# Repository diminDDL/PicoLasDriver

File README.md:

# Picolas Laser Diode Controller/Driver

This repository houses the necessary components for a touchscreen-based controller/driver for the Picolas series of laser diode boards, including hardware schematics, embedded firmware, and a Python GUI.

## Features

- Supports control of analog models with trigger pins and analog voltage for adjusting the current setpoint.
- Designed to work seamlessly with a Raspberry Pi SBC and a touchscreen.
- Configuration flexibility through JSON file.

## Getting Started

### Prerequisites

- Raspberry Pi with a touchscreen
- Picolas series laser diode board (analog models with trigger pins)

### Installation

1. Clone the repository.
2. Follow the setups in [howto.md](https://github.com/diminDDL/PicoLasDriver/blob/main/howto.md)
3. Configure a startup script to initiate the Python program automatically on boot. Additionally, it's advisable to disable the touchscreen until the program starts.
4. Consider enabling the overlay filesystem to safeguard your data.

## GUI Layout & Functions

- **"+" and "-" buttons**: Increase or decrease values. They accelerate when held.
- **"Single/Pulsed" modes**: Toggle single pulse operation.
- **"Global/Local pulse count"**: View total pulse count and current session count.
- **"ADC readout"**: Display the raw 12-bit ADC value from the photodiode amplifier.
- **"Lock icon"**: Lock or unlock the device to prevent accidental value changes.
- **"IO1-4"**: IO pin toggle buttons.
- **"Enable/Disable"**: Control the pulse output.
- **Error readout**: Reads out the errors and other state information.

⚠️ **Important**: It is recommended to turn off the output when adjusting settings to prevent potential glitches on the output.

## Hardware & Communication

- The board connects to the Raspberry Pi via USB, with a communication frequency of every 100ms.
- Auto-reconnect and fault indications in the Python GUI.
- LED indicators for the board's internal states.
- GPIO pins provide a high impedance 5V when active.
- Over-voltage protection up to 5V.
- Photodiode amplifier module design and guidance provided.

### Pinout of the connector:

## Operating Mechanism

The board keeps the Picolas driver's enable pin high and uses the trigger pin to generate impulses. An analog DAC sets the voltage to control the output current limit. If the E-STOP pin is triggered, the system becomes non-functional until a power cycle.

## License

This project is licensed under the MIT License.

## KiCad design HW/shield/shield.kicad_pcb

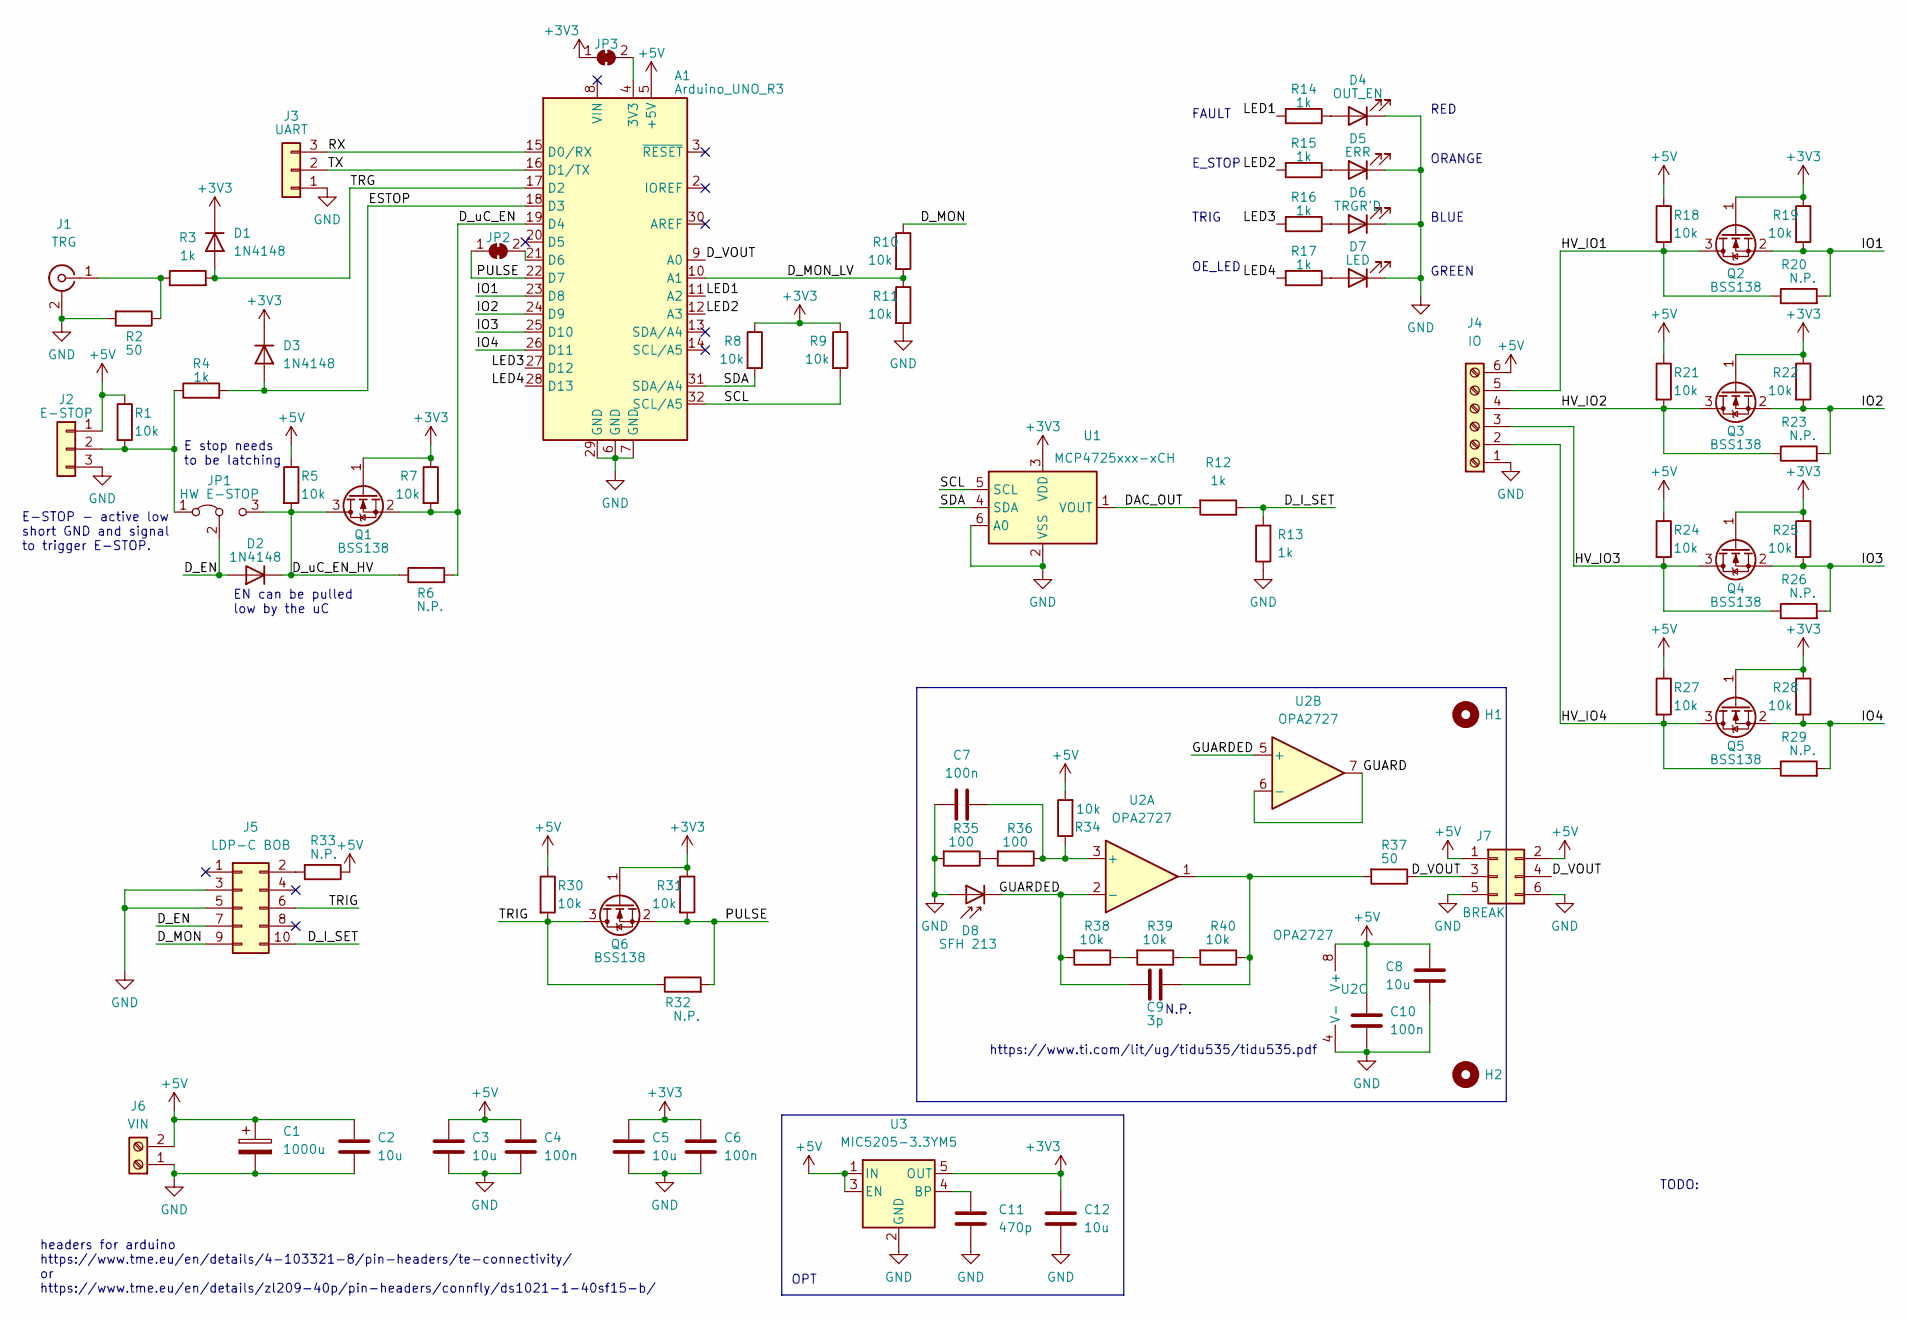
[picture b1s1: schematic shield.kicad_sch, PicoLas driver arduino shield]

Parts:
A1: Arduino_UNO_R3
C1: 1000u; CP_Elec_10x10
C2, C3, C5, C8, C12: 10u; C_0805_2012Metric_Pad1.18x1.45mm_HandSolder
C4, C6, C7, C10: 100n; C_0805_2012Metric_Pad1.18x1.45mm_HandSolder
C9: 3p; C_0805_2012Metric_Pad1.18x1.45mm_HandSolder
C11: 470p; C_0805_2012Metric_Pad1.18x1.45mm_HandSolder
D1, D2, D3: 1N4148; D_SOD-123
D4: OUT_EN; LED_0805_2012Metric_Pad1.15x1.40mm_HandSolder
D5: ERR; LED_0805_2012Metric_Pad1.15x1.40mm_HandSolder
D6: TRGR'D; LED_0805_2012Metric_Pad1.15x1.40mm_HandSolder
D7: LED; LED_0805_2012Metric_Pad1.15x1.40mm_HandSolder
D8: SFH 213; LED_D5.0mm_IRGrey
H1, H2: MountingHole; MountingHole_3.2mm_M3
J1: TRG; SMA_Amphenol_901-144_Vertical
J2: E-STOP; TerminalBlock_Altech_AK300-3_P5.00mm
J3: UART; PinSocket_1x03_P2.54mm_Vertical
J4: IO; Altech_AK300_1x06_P5.00mm_45-Degree
J5: LDP-C BOB; PinHeader_2x05_P2.54mm_Vertical
J6: VIN; TerminalBlock_Altech_AK300-2_P5.00mm
J7: BREAK; PinSocket_2x03_P2.54mm_Vertical
JP1: HW E-STOP; SolderJumper-3_P1.3mm_Bridged12_RoundedPad1.0x1.5mm_NumberL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
JP2, JP3: INTR; SolderJumper-2_P1.3mm_Bridged2Bar_RoundedPad1.0x1.5mm
Q1, Q2, Q3, Q4, Q5, Q6: BSS138; SOT-23
R1, R5, R7, R8, R9, R10, R11, R18, R19, R21, R22, R24, R25, R27, R28, R30, R31, R34, R38, R39, R40: 10k; R_0805_2012Metric_Pad1.20x1.40mm_HandSolder
R2, R37: 50; R_0805_2012Metric_Pad1.20x1.40mm_HandSolder
R3, R4, R12, R13, R14, R15, R16, R17: 1k; R_0805_2012Metric_Pad1.20x1.40mm_HandSolder
R6, R20, R23, R26, R29, R32, R33: N.P.; R_0805_2012Metric_Pad1.20x1.40mm_HandSolder
R35, R36: 100; R_0805_2012Metric_Pad1.20x1.40mm_HandSolder
U1: MCP4725xxx-xCH; SOT-23-6
U2: OPA2727; SO-8_3.9x4.9mm_P1.27mm
U3: MIC5205-3.3YM5; SOT-23-5

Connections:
+3V3: C5.1, C6.1, C12.1, D1.1 (K), D3.1 (K), JP3.1 (A), Q1.1 (G), Q2.1 (G), Q3.1 (G), Q4.1 (G), Q5.1 (G), Q6.1 (G), R7.1, R8.1, R9.1, R19.1, R22.1, R25.1, R28.1, R31.1, U1.3 (VDD), U3.5 (OUT)
+5V: A1.5 (+5V), C1.1, C2.1, C3.1, C4.1, C8.1, C10.1, J2.1, J4.6, J6.2, J7.1, J7.2, R1.1, R5.1, R18.1, R21.1, R24.1, R27.1, R30.1, R33.1, R34.2, U2.8 (V+), U3.1 (IN), U3.3 (EN)
/DAC_OUT: R12.2, U1.1 (VOUT)
/D_EN: D2.2 (A), J5.7, JP1.2 (C)
/D_I_SET: J5.10, R12.1, R13.2
/D_MON: J5.9, R10.1
/D_MON_LV: A1.10 (A1), R10.2, R11.1
/D_VOUT: A1.9 (A0), J7.3, J7.4, R37.1
/D_uC_EN: A1.19 (D4), Q1.2 (S), R6.2, R7.2
/D_uC_EN_HV: D2.1 (K), JP1.3 (B), Q1.3 (D), R5.2, R6.1
/ESTOP: A1.18 (D3), D3.2 (A), R4.2
/GUARD: U2.6 (-), U2.7
/GUARDED: C9.1, D8.1 (K), R38.2, U2.2 (-), U2.5 (+)
/HV_IO1: J4.5, Q2.3 (D), R18.2, R20.1
/HV_IO2: J4.4, Q3.3 (D), R21.2, R23.1
/HV_IO3: J4.3, Q4.3 (D), R24.2, R26.1
/HV_IO4: J4.2, Q5.3 (D), R27.2, R29.1
/IO1: A1.23 (D8), Q2.2 (S), R19.2, R20.2
/IO2: A1.24 (D9), Q3.2 (S), R22.2, R23.2
/IO3: A1.25 (D10), Q4.2 (S), R25.2, R26.2
/IO4: A1.26 (D11), Q5.2 (S), R28.2, R29.2
/LED1: A1.11 (A2), R14.2
/LED2: A1.12 (A3), R15.2
/LED3: A1.27 (D12), R16.2
/LED4: A1.28 (D13), R17.2
/PULSE: A1.22 (D7), JP2.1 (A), Q6.2 (S), R31.2, R32.2
/RX: A1.15 (D0/RX), J3.3
/SCL: A1.32 (SCL/A5), R9.2, U1.5 (SCL)
/SDA: A1.31 (SDA/A4), R8.2, U1.4 (SDA)
/TRG: A1.17 (D2), D1.2 (A), R3.2
/TRIG: J5.6, Q6.3 (D), R30.2, R32.1
/TX: A1.16 (D1/TX), J3.2
GND: A1.6 (GND), A1.7 (GND), A1.29 (GND), C1.2, C2.2, C3.2, C4.2, C5.2, C6.2, C7.1, C8.2, C10.2, C11.1, C12.2, D4.1 (K), D5.1 (K), D6.1 (K), D7.1 (K), D8.2 (A), J1.2 (Ext), J2.3, J3.1, J4.1, J5.3, J5.5, J6.1, J7.5, J7.6, R2.2, R11.2, R13.1, R35.2, U1.2 (VSS), U1.6 (A0), U2.4 (V-), U3.2 (GND)
unnamed: A1.4 (3V3), JP3.2 (B)
unnamed: A1.21 (D6), JP2.2 (B)
unnamed: C7.2, R34.1, R36.1, U2.3 (+)
unnamed: C9.2, R37.2, R40.1, U2.1
unnamed: C11.2, U3.4 (BP)
unnamed: D4.2 (A), R14.1
unnamed: D5.2 (A), R15.1
unnamed: D6.2 (A), R16.1
unnamed: D7.2 (A), R17.1
unnamed: J1.1 (In), R2.1, R3.1
unnamed: J2.2, JP1.1 (A), R1.2, R4.1
unnamed: J5.2, R33.2
unnamed: R35.1, R36.2
unnamed: R38.1, R39.2
unnamed: R39.1, R40.2

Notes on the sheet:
OPT
FAULT
BLUE
ORANGE
TODO:
OE_LED
E stop needs to be latching
headers for arduino https://www.tme.eu/en/details/4-103321-8/pin-headers/te-connectivity/ or https://www.tme.eu/en/details/zl209-40p/pin-headers/connfly/ds1021-1-40sf15-b/
N.P.
EN can be pulled low by the uC
TRIG
E_STOP
RED
https://www.ti.com/lit/ug/tidu535/tidu535.pdf
E-STOP - active low short GND and signal to trigger E-STOP.
GREEN

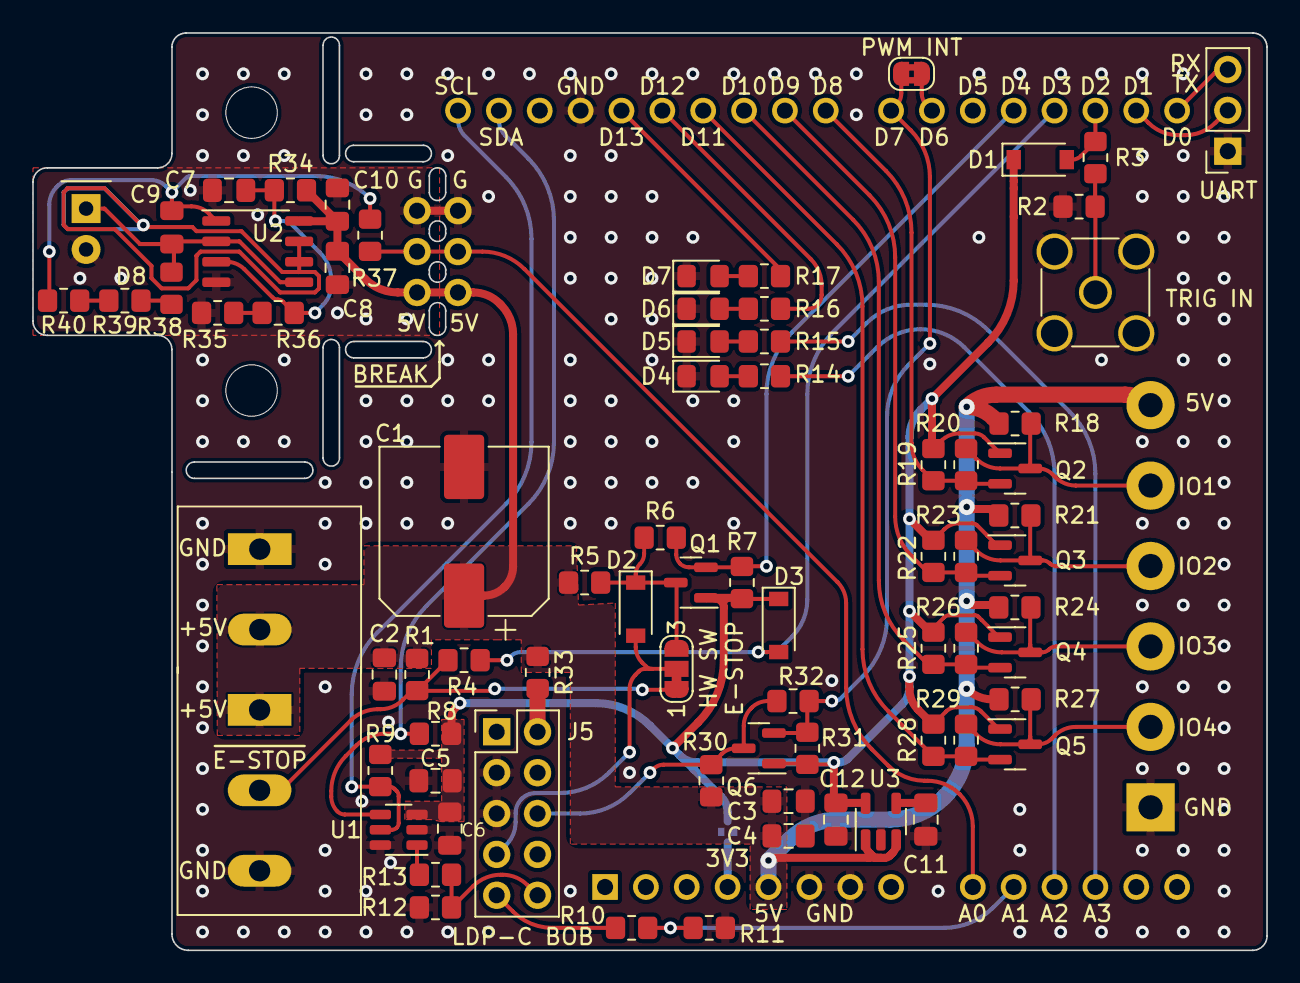
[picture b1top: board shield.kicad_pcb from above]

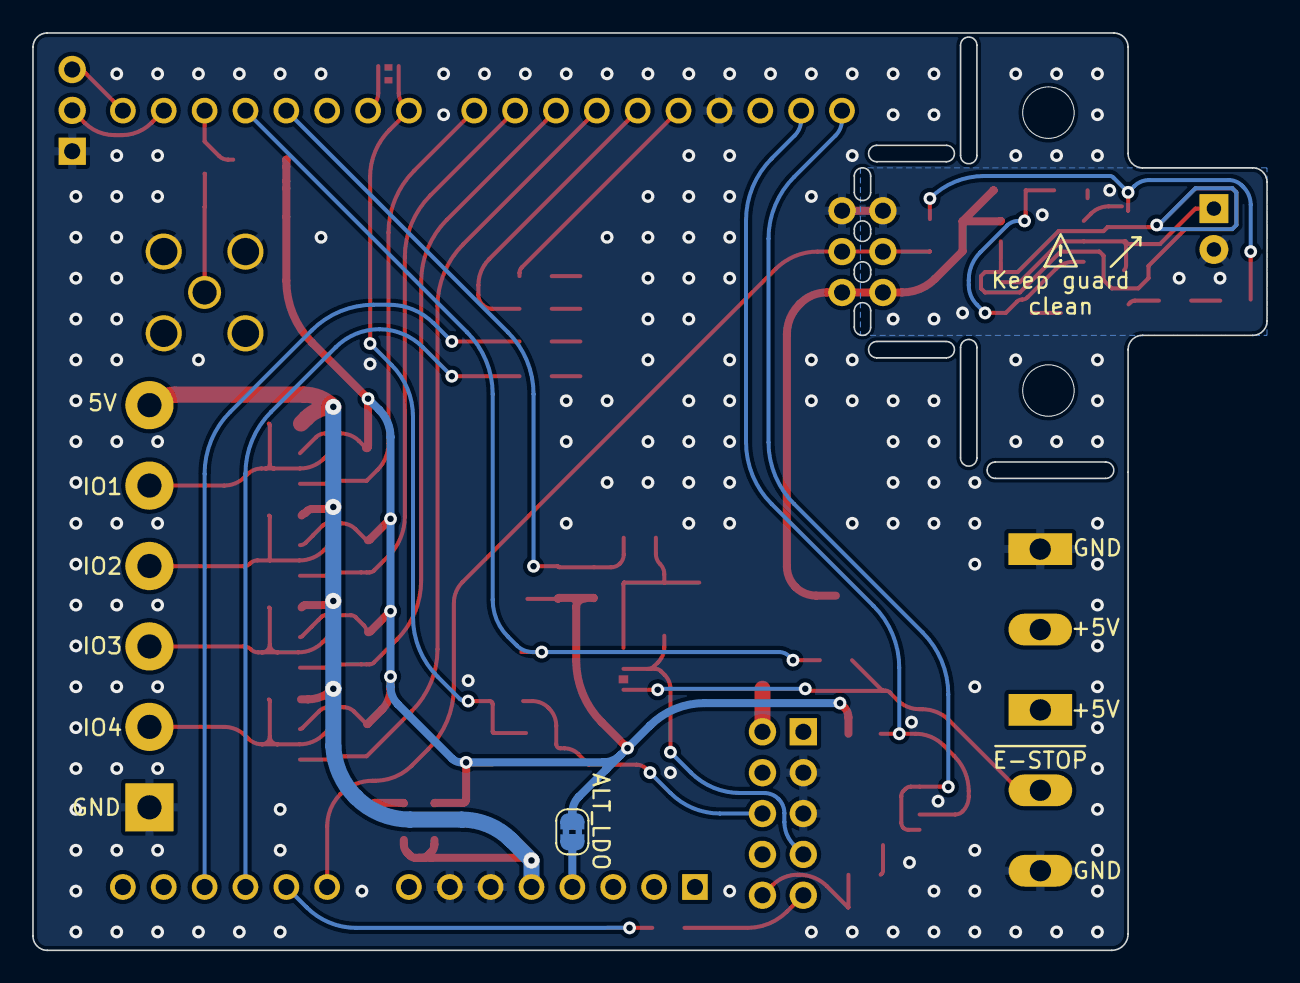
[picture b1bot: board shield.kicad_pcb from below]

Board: 2 copper layers, 76.7 x 57.0 mm, 82 parts (2 on the bottom side), 48 nets.

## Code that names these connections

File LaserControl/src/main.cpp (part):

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#define SERIAL_MODE SERIAL_8E1
#define FORWARD_PORT Serial1                // when in digital mode all the communication will be forwarded to this port
#define INTERRUPT_PIN 2                     // interrupt pin for the trigger
#define ESTOP_PIN 3                         // emergency stop pin, active low
#define EN_PIN 4                            // enable pin, active high
#define PULSE_PIN pwm<pwm_pin::PWML6_PC23>  // pin used to generate the pulses
#define PULSE_PIN_STD 7                     // pin used to generate the pulses in standard notation
#define PULSE_COUNT_PIN 6                   // pin used to count the pulses
#define GPIO_BASE_PIN 8                     // base pin for the GPIO outputs
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#define DAC_VREF 3.3                        // DAC reference voltage
#define DAC_VDIV 2                          // DAC voltage divider ratio 2 means we are using a 1:2 divider aka the output is half the input
#define ADC_PIN A0                          // pin used to read the photodiode
PULSE_PIN pulsePin;                         // pulse pin object
Communications comms(&Serial, &FORWARD_PORT, SERIAL_BAUD_RATE, SERIAL_MODE); // communications object
Memory memory;                              // memory object
MCP4725 MCP(0x60, &Wire1);                  // init DAC         
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    }
    digitalWrite(57, running);
    digitalWrite(TRIG_LED, LOW);
    attachInterrupt(digitalPinToInterrupt(INTERRUPT_PIN), trg, CHANGE);
}

void pulse(){
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    }
    pinMode(EN_PIN, OUTPUT);
    digitalWrite(EN_PIN, HIGH);
    pinMode(ESTOP_PIN, INPUT);   // TODO attach interrupt to this pin
    attachInterrupt(digitalPinToInterrupt(ESTOP_PIN), dummy_pulse, RISING);
    detachInterrupt(digitalPinToInterrupt(ESTOP_PIN));
    delay(1);
    attachInterrupt(digitalPinToInterrupt(ESTOP_PIN), stop, FALLING);
    pinMode(OE_LED, OUTPUT);
    pinMode(TRIG_LED, OUTPUT);
    pinMode(E_STOP_LED, OUTPUT);
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            pulsePin.stop();
            if(!enabled){
                // this cursed code is to prevent the interrupt from firing when we attach it
                attachInterrupt(digitalPinToInterrupt(INTERRUPT_PIN), trg, CHANGE);
                delay(1);
                attachInterrupt(digitalPinToInterrupt(PULSE_COUNT_PIN), dummy_pulse, CHANGE);
                detachInterrupt(digitalPinToInterrupt(PULSE_COUNT_PIN));
                delay(1);
                attachInterrupt(digitalPinToInterrupt(PULSE_COUNT_PIN), pulse, CHANGE);
                enabled = true;
            }
            // edge case, if the trigger is already high we need to start the PWM
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
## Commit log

2022-10-12 set up microcontroller env and script for controlling touch input
2022-10-13 working async UI example
2022-10-13 removed vscode file
2022-10-14 updated UI
2022-10-19 added fix for UI not being fullscreen on the rpi
2022-10-19 added cursor removal
2022-10-21 added more stuff to UI and fixed a few bugs
2022-10-24 some minor updates
2022-10-25 added GPIO buttons and an error readout
2022-10-28 GUI finished
2022-10-28 replaced match to legacy if else
2022-10-28 improved layout
2022-10-28 added fullscheen parameter
2022-11-12 minor update
2022-11-12 serial test working
2022-11-16 working serial reading function
2022-11-16 updated protocl handling
2022-11-25 added the other driver and code to handle other controll schemes
2022-11-25 added some more driver details and proper async even loop
2022-11-25 changed some comms things
2022-11-27 removed some redundant stuff
2022-11-29 updated parser
2022-12-01 added more serial parsing
2022-12-02 working command parser
2022-12-09 response messages are now compliant with the protocol
2022-12-15 some changes
2022-12-18 added max current variable to scale the analog output
2022-12-27 added some notes on future implementation
2022-12-28 added libraries for PWM controll
2023-01-04 added BOM cost, removed PWM DAC stuff, updated some logic
2023-01-10 added stuff to schematic
2023-01-10 added note about e-stop
2023-01-12 added simulation and started woking on photodiode amp
2023-01-12 finished schematic
2023-01-13 changed op amp added simulation of photodiode
2023-01-13 small schematic changes
2023-01-14 added rudamentary pulse generation
2023-01-18 started PCB
2023-01-18 improved guard
2023-01-19 PCB layout
2023-01-20 routing
2023-01-20 PCB routing finished, needs checking
2023-01-21 PCB done
2023-01-23 added LDO, BOM
2023-01-24 gerber files and BOM
2023-01-24 added pin headers
2023-02-16 fixed flipped I2C lines in the board files
2023-02-17 Added minimal EEPROM code
2023-02-21 starting refactoring
2023-02-21 moved comms into separate class
2023-02-22 basic EEPROM functions abstracted into a separate class
2023-02-22 updated kicad files to 7.0
2023-02-24 basic wear leveling write working
2023-02-28 semi working wear leveling read implementation
2023-03-05 wear leveling read and write working
2023-03-06 testing wear leveling
2023-03-06 wear leveling small changes
2023-03-07 wear leveling bad sector detection seems to be working, more tesitng needed
2023-03-10 wear leveling with bad pages working
2023-03-14 working wear leveling, bot won't work if edges of memory are broken!
2023-03-17 fixed cases if upper most page gets corrupted
2023-03-17 wear leveling working
2023-03-17 cleaned up code a bit
2023-03-18 wear leveling fully working
2023-03-21 finshed DAC, started working on PWM (I hate microchip)
2023-03-24 fixed PWM
2023-03-27 added eprom, fixed serial parsing bug and improved PWM system
2023-03-28 fixed counter interrupt, added local counter
2023-04-03 added ADC readout and estop handling
2023-04-05 added some stuff regarding modes and found some new bugs
2023-04-20 starting a rewrite for the rp2040
2023-05-03 added HAL for the FRAM memory
2023-05-11 updated memory and mcp code
2023-05-13 added softPWM module for low frequencies
2023-05-13 porting to picosdk
2023-05-25 wip porting to picosdk
2023-05-25 ported most things
2023-05-25 added DAC library
2023-05-28 begun integration with the GUI
2023-05-29 minor changes in the structure
2023-05-29 minimal working application
2023-07-07 added async skeleton to the serial comms
2023-07-09 fixed the new async structure and added safeguards
2023-07-09 async skeleton working
2023-07-10 improved serial data sending
2023-07-18 significantly improved serial comms fixing several bugs
2023-07-20 added readback on startup
2023-07-24 fixed IO and improved error handling
2023-07-24 tested on real hardware, updated the guide
2023-07-25 added pulse mode to firmware
2023-07-26 implemented single mode, improved EEPROM handling and added a few service commands
2023-07-27 added pulse mode to the GUI and removed debug statemetns from the firmware
2023-07-27 added some error handling
2023-07-28 fixel pulse length issues
2023-07-29 added timeout and error handling
2023-07-30 final version using a mix of soft and hard PIO PWM
2023-07-30 fixed soft PWM long bug, improved GUI data loading
2023-08-11 added screenshots, adjusted schematics for better layout
